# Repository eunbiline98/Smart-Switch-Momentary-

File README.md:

# Smart Switch Momentary

DIY Smart Switch momentary 2 Gang and 2 Channel Relay SPDT

List Item

- Esp8266 (Wemos D1 Mini) / Chip SoC Esp8266
- Relay 5VDC SPDT Songle (Max Current 10A)
- Power Module Hi-Link 220VAC to 5VDC
- Resistor 1k, 10K (SMD 0805)
- Diode 1N4007 SMD
- Transistor 2n2222a
- Terminal Screw 6 Pin Hole
- Push Button (schneider momentary switch) Datasheet: https://download.schneider-electric.com/files?p_enDocType=Instruction+sheet&p_File_Name=MS18524.pdf&p_Doc_Ref=MS18524

# Schematic

# Layout 
### Top View 

### Bottom View

# Home Assistant

Under covers in HA, use this config

```
mqtt:
  broker: "Your IP Broker/server"
  port: Your port MQTT
  username: "Your username"
  password: Your password

switch:
  - platform: mqtt
    name: "General Lamp"
    state_topic: "switch/bedroom1/1/state"
    command_topic: "switch/1/command"
    payload_on: "1"
    payload_off: "0"

 switch:
  - platform: mqtt
    name: "Cove Lighting"
    state_topic: "switch/bedroom1/2/state"
    command_topic: "switch/2/command"
    payload_on: "1"
    payload_off: "0"
```

# Reference

- WiFi Manager (https://github.com/tzapu/WiFiManager)
- MQTT (https://github.com/knolleary/pubsubclient)

# Update

- DIY_switch_3_gang_Ver_1_0 (Test Board Circuit)
- DIY_switch_3_gang_Ver_1_0_WM (Update Feature WifI Manager)
- DIY_switch_3_gang_Ver_1_1_WM (Update Last State Condition Dashboard Home Assistant)
- DIY_switch_3_gang_Ver_1_2_WM (Update Feature WiFi and Mqtt Config Manager)

# Dimension

- L = 69,84 mm
- W = 70,87 mm

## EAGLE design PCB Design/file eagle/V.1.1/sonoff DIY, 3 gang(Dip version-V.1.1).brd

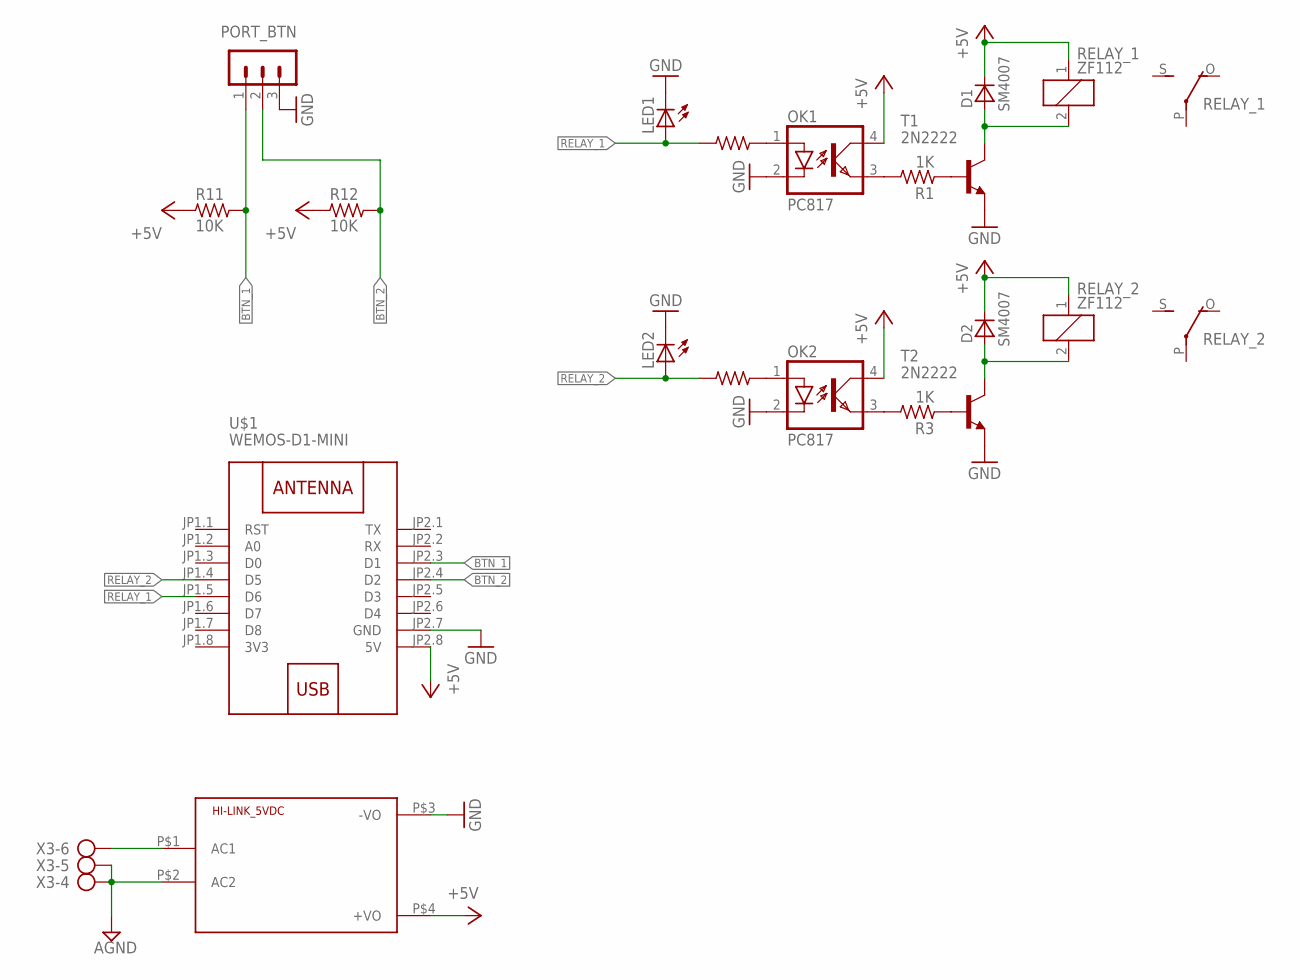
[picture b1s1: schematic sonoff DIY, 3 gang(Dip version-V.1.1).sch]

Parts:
D1, D2: SM4007; MELF-MLL41
HI-LINK_5VDC: HLK-PM013W; HLK-PM01
LED1, LED2: LED3MM
OK1, OK2: PC817; DIL04
PORT_BTN: MA03-1
R1, R2, R3, R4: 1K; R0805
R11, R12: 10K; R0805
RELAY_1, RELAY_2: ZF112
T1, T2: 2N2222; TO18
U$1: WEMOS-D1-MINI
X3: SMKDSP_1,5/6

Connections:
3V3: U$1.JP1.8 (3V3)
+5V: D1.C, D2.C, HI-LINK_5VDC.P$4 (+VO), OK1.4 (COL), OK2.4 (COL), R11.1, R12.1, RELAY_1.1, RELAY_2.1, U$1.JP2.8 (5V)
AGND: HI-LINK_5VDC.P$2 (AC2), X3.4, X3.5
BTN_1: PORT_BTN.1, R11.2, U$1.JP2.3 (D1)
BTN_2: PORT_BTN.2, R12.2, U$1.JP2.4 (D2)
GND: HI-LINK_5VDC.P$3 (-VO), LED1.K (C), LED2.K (C), OK1.2 (C), OK2.2 (C), PORT_BTN.3, T1.1 (E), T2.1 (E), U$1.JP2.7 (GND)
unnamed: OK1.1 (A), R2.1
unnamed: OK1.3 (EMIT), R1.2
unnamed: R1.1, T1.2 (B)
unnamed: D1.A, RELAY_1.2, T1.3 (C)
unnamed: OK2.1 (A), R4.1
unnamed: HI-LINK_5VDC.P$1 (AC1), X3.6
unnamed: OK2.3 (EMIT), R3.2
unnamed: R3.1, T2.2 (B)
unnamed: D2.A, RELAY_2.2, T2.3 (C)
RELAY_1: LED1.A, R2.2, U$1.JP1.5 (D6)
RELAY_2: LED2.A, R4.2, U$1.JP1.4 (D5)

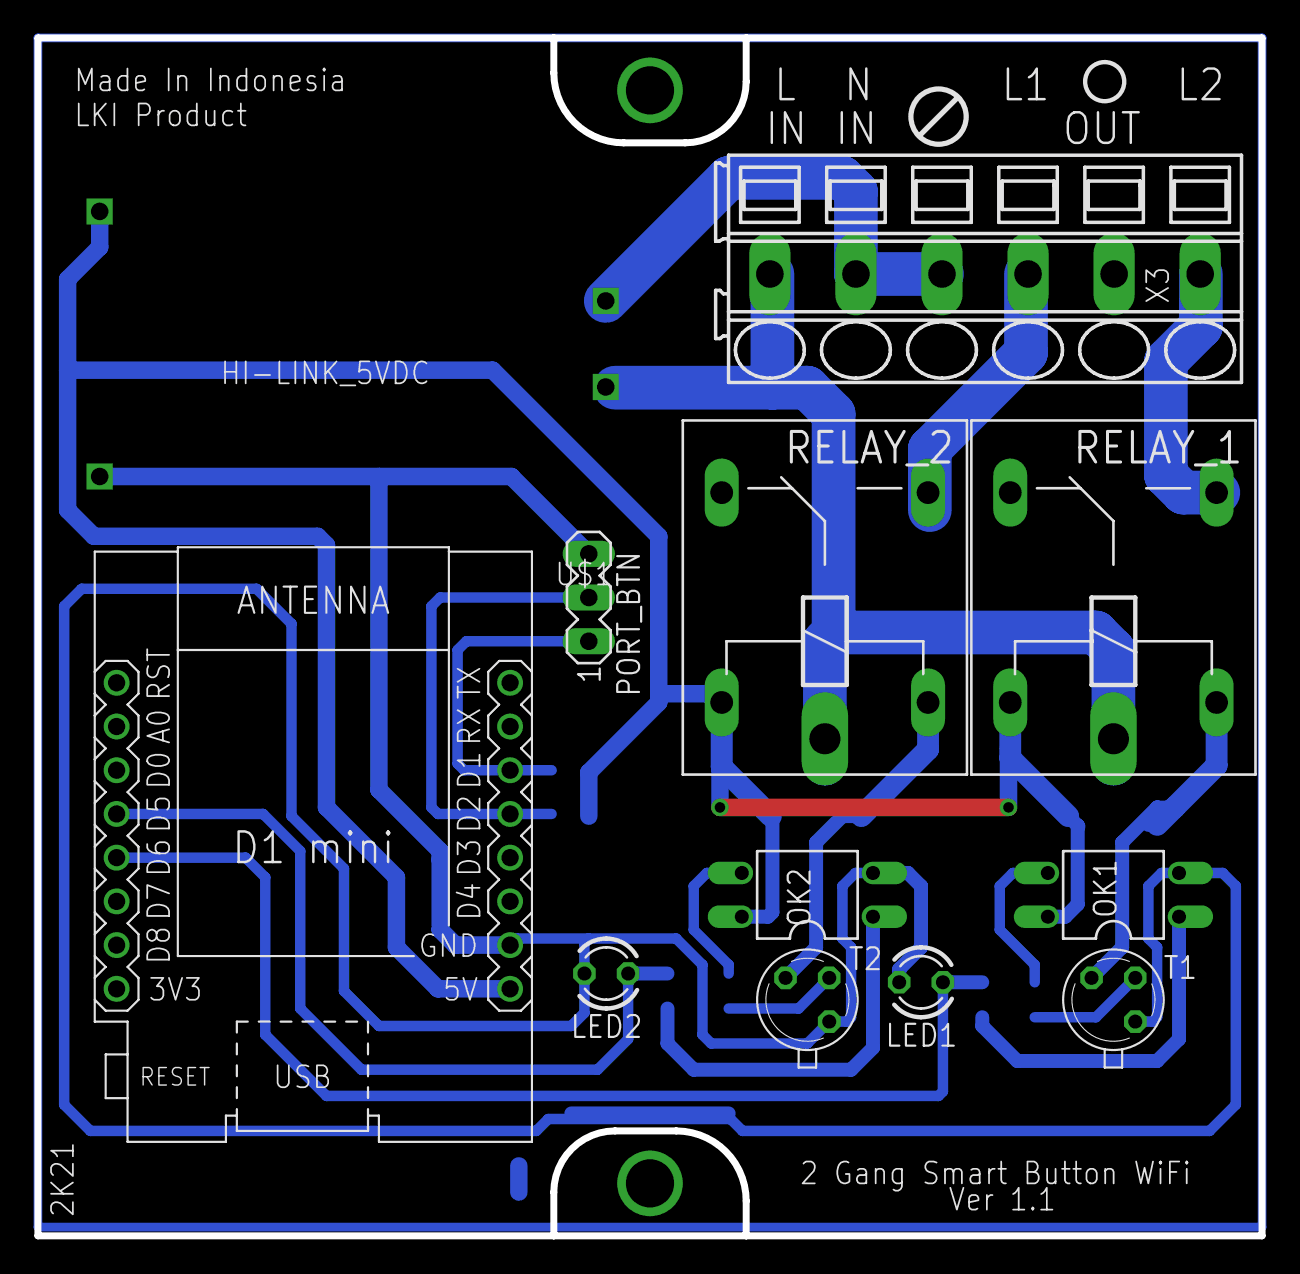
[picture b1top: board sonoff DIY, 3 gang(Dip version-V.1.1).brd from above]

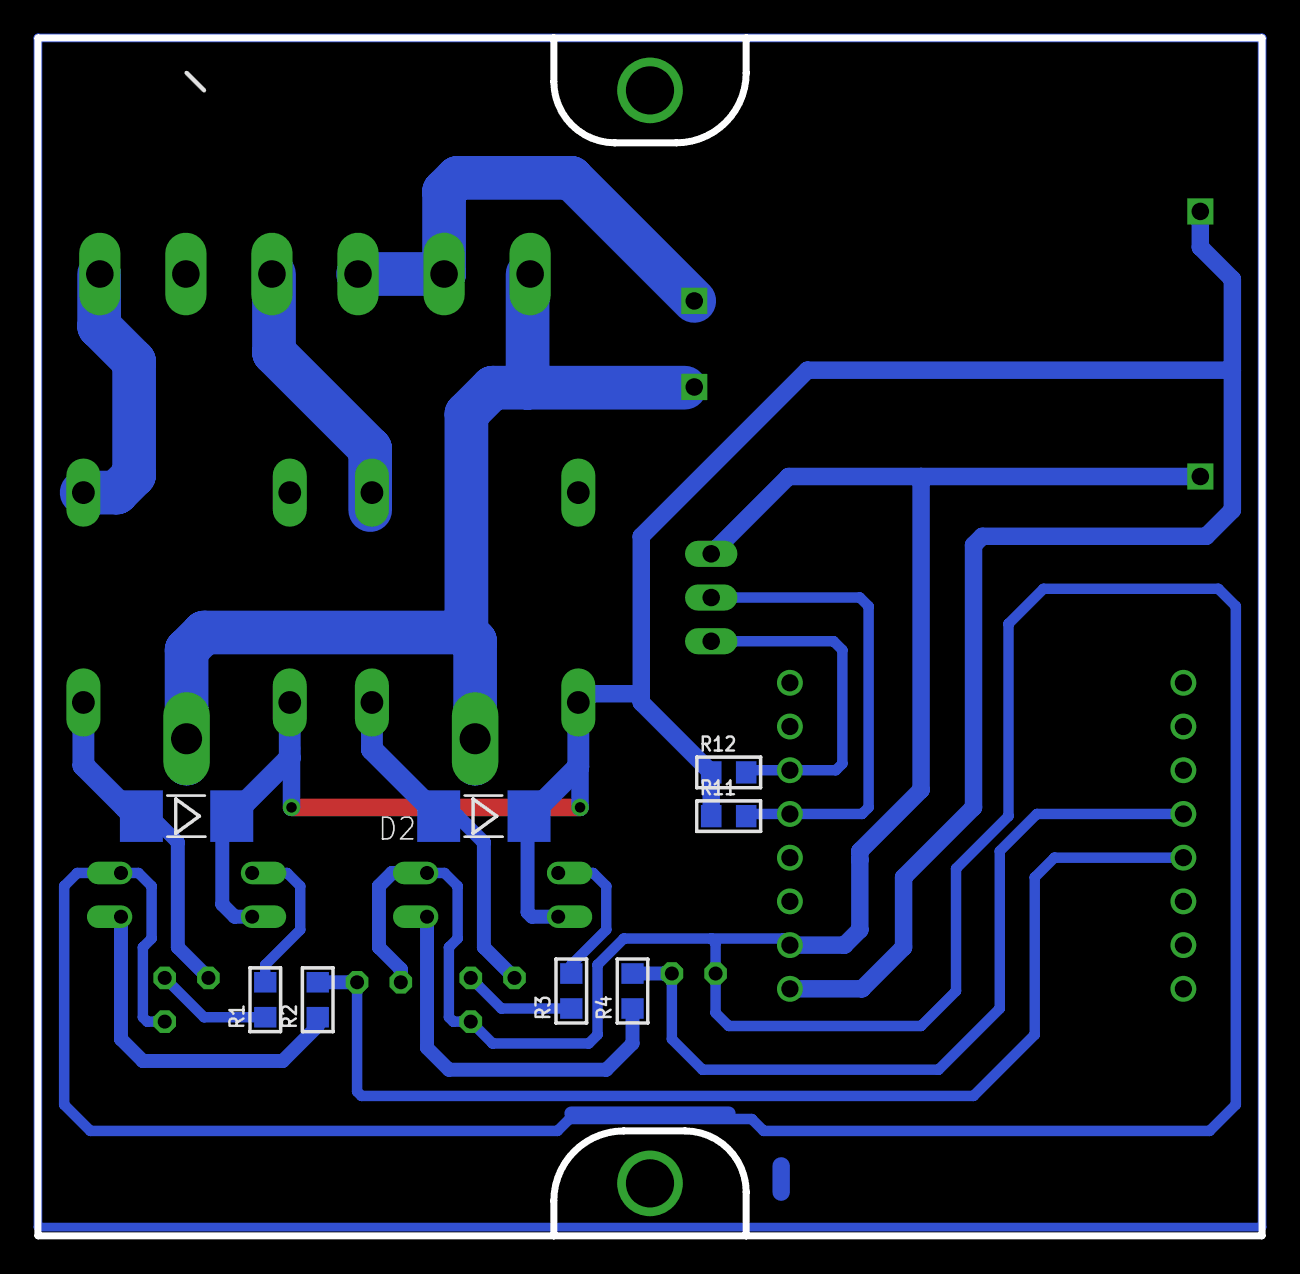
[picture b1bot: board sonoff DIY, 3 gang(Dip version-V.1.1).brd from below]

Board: 2 copper layers, 71.1 x 69.6 mm, 20 parts (8 on the bottom side), 16 nets.

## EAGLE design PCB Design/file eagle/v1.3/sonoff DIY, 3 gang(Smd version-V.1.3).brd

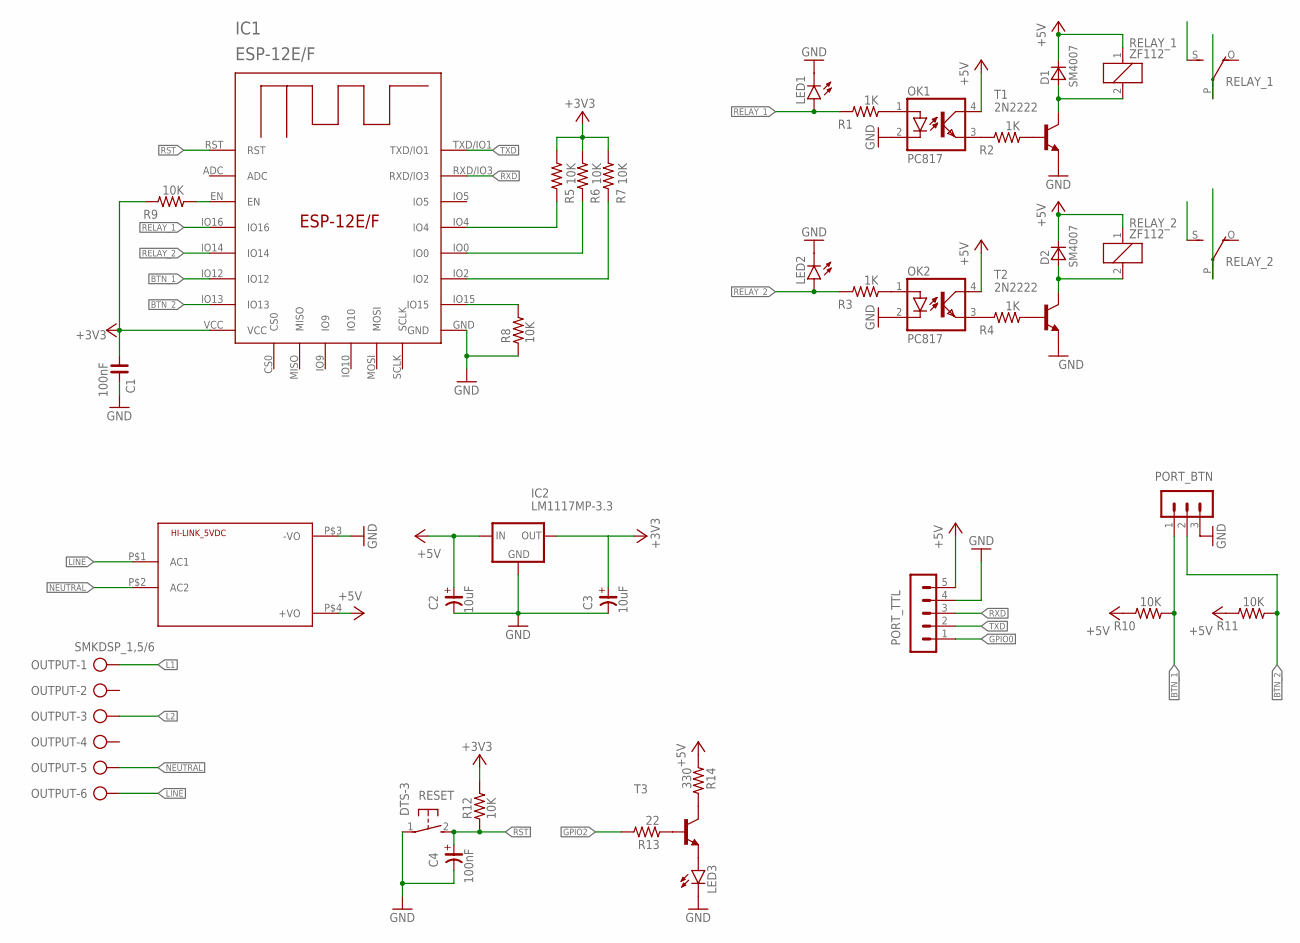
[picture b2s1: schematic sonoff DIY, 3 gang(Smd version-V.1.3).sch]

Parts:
C1: 100nF; C0805
C2, C3: 10uF; C3528/T
C4: 100nF; C3528/T
D1, D2: SM4007; MELF-MLL41
HI-LINK_5VDC: HLK-PM013W; HLK-PM01
IC1: ESP-12E/F; ESP-12E
IC2: LM1117MP-3.3; SOT223
LED1, LED2, LED3: LED3MM
OK1, OK2: PC817; DIL04
OUTPUT: SMKDSP_1,5/6
PORT_BTN: MA03-1
PORT_TTL: MA05-1
R1, R2, R3, R4: 1K; R0805
R5, R6, R7, R8, R9, R10, R11, R12: 10K; R0805
R13: 22; R0805
R14: 330; R0805
RELAY_1, RELAY_2: ZF112
RESET: DTS-3
T1, T2: 2N2222; TO18
T3: BC817-16LT1-NPN-SOT23-BEC; SOT23-BEC

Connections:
+3V3: C1.1, C3.+, IC1.VCC, IC2.2 (OUT), IC2.4 (OUT), R5.1, R6.1, R7.1, R9.2, R12.2
+5V: C2.+, D1.C, D2.C, HI-LINK_5VDC.P$4 (+VO), IC2.3 (IN), OK1.4 (COL), OK2.4 (COL), PORT_TTL.5, R10.2, R11.2, R14.1, RELAY_1.1, RELAY_2.1
BTN_1: IC1.IO12, PORT_BTN.1, R10.1
BTN_2: IC1.IO13, PORT_BTN.2, R11.1
GND: C1.2, C2.-, C3.-, C4.-, HI-LINK_5VDC.P$3 (-VO), IC1.GND, IC2.1 (GND), LED1.K (C), LED2.K (C), LED3.K (C), OK1.2 (C), OK2.2 (C), PORT_BTN.3, PORT_TTL.4, R8.1, RESET.1, T1.1 (E), T2.1 (E)
GPIO0: IC1.IO0, PORT_TTL.1, R6.2
GPIO2: IC1.IO2, R7.2, R13.2
L1: OUTPUT.1, RELAY_1.S
L2: OUTPUT.3, RELAY_2.S
LINE: HI-LINK_5VDC.P$1 (AC1), OUTPUT.6, RELAY_1.P, RELAY_2.P
unnamed: OK1.3 (EMIT), R2.2
unnamed: R2.1, T1.2 (B)
unnamed: OK2.1 (A), R3.1
unnamed: D1.A, RELAY_1.2, T1.3 (C)
unnamed: OK2.3 (EMIT), R4.2
unnamed: R4.1, T2.2 (B)
unnamed: OK1.1 (A), R1.1
unnamed: IC1.IO4, R5.2
unnamed: D2.A, RELAY_2.2, T2.3 (C)
unnamed: LED3.A, T3.E
unnamed: IC1.IO15, R8.2
unnamed: R13.1, T3.B
unnamed: IC1.EN, R9.1
unnamed: R14.2, T3.C
NEUTRAL: HI-LINK_5VDC.P$2 (AC2), OUTPUT.5
RELAY_1: IC1.IO16, LED1.A, R1.2
RELAY_2: IC1.IO14, LED2.A, R3.2
RST: C4.+, IC1.RST, R12.1, RESET.2
RXD: IC1.RXD/IO3, PORT_TTL.3
TXD: IC1.TXD/IO1, PORT_TTL.2

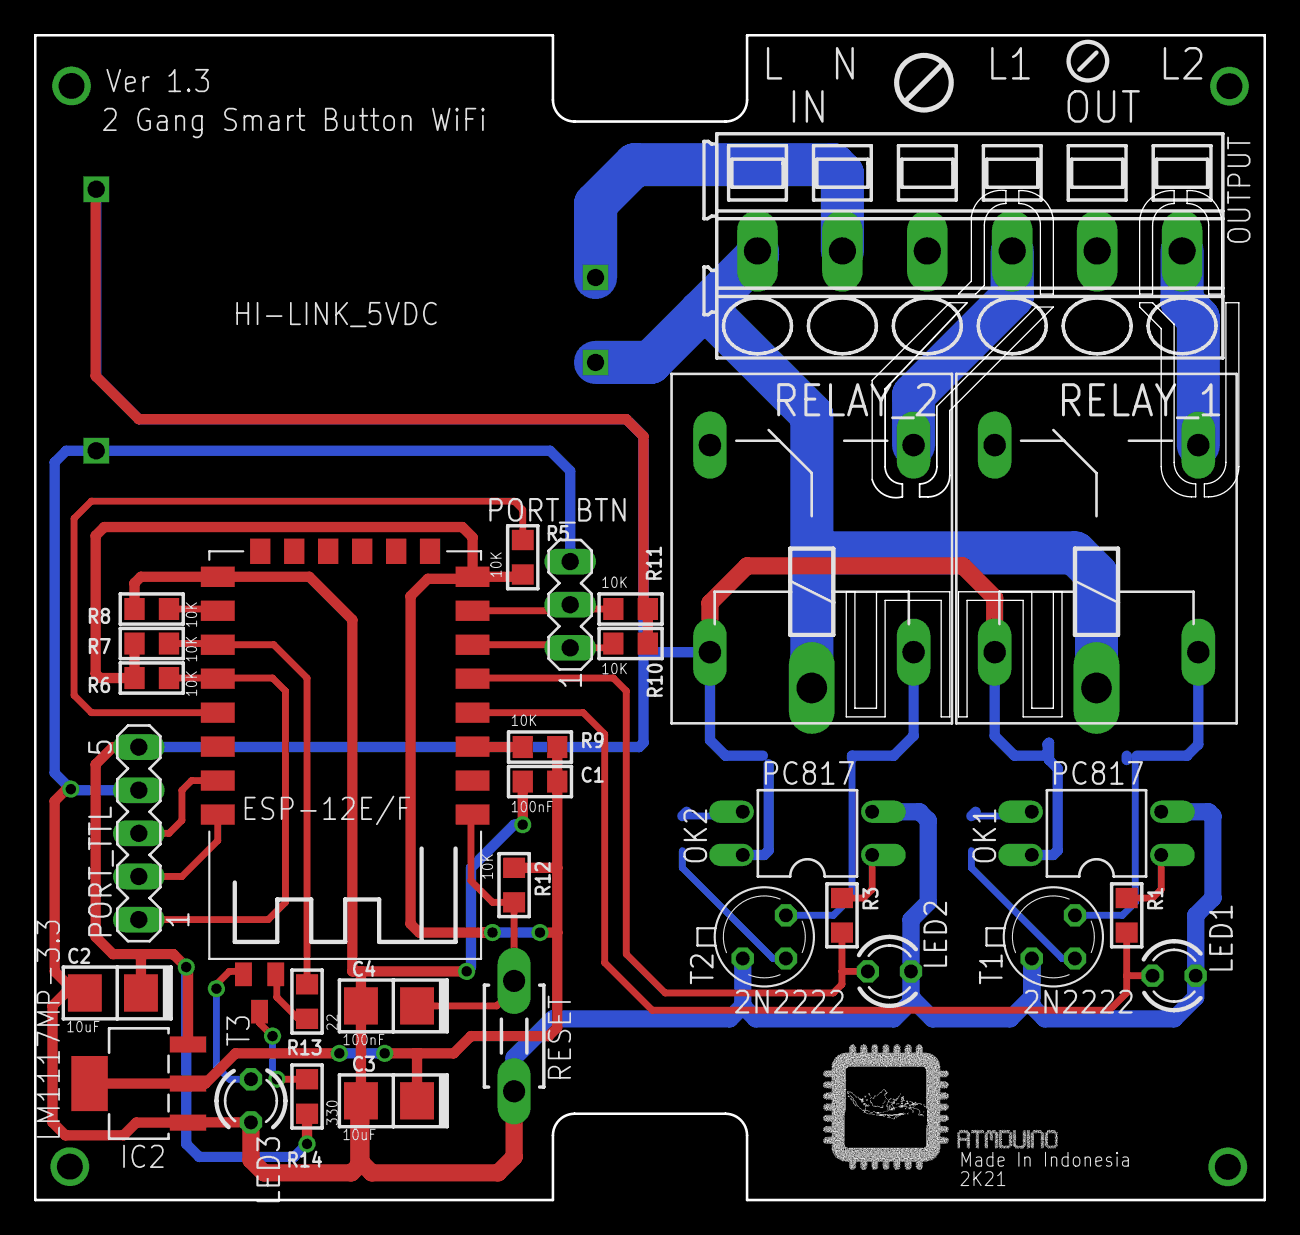
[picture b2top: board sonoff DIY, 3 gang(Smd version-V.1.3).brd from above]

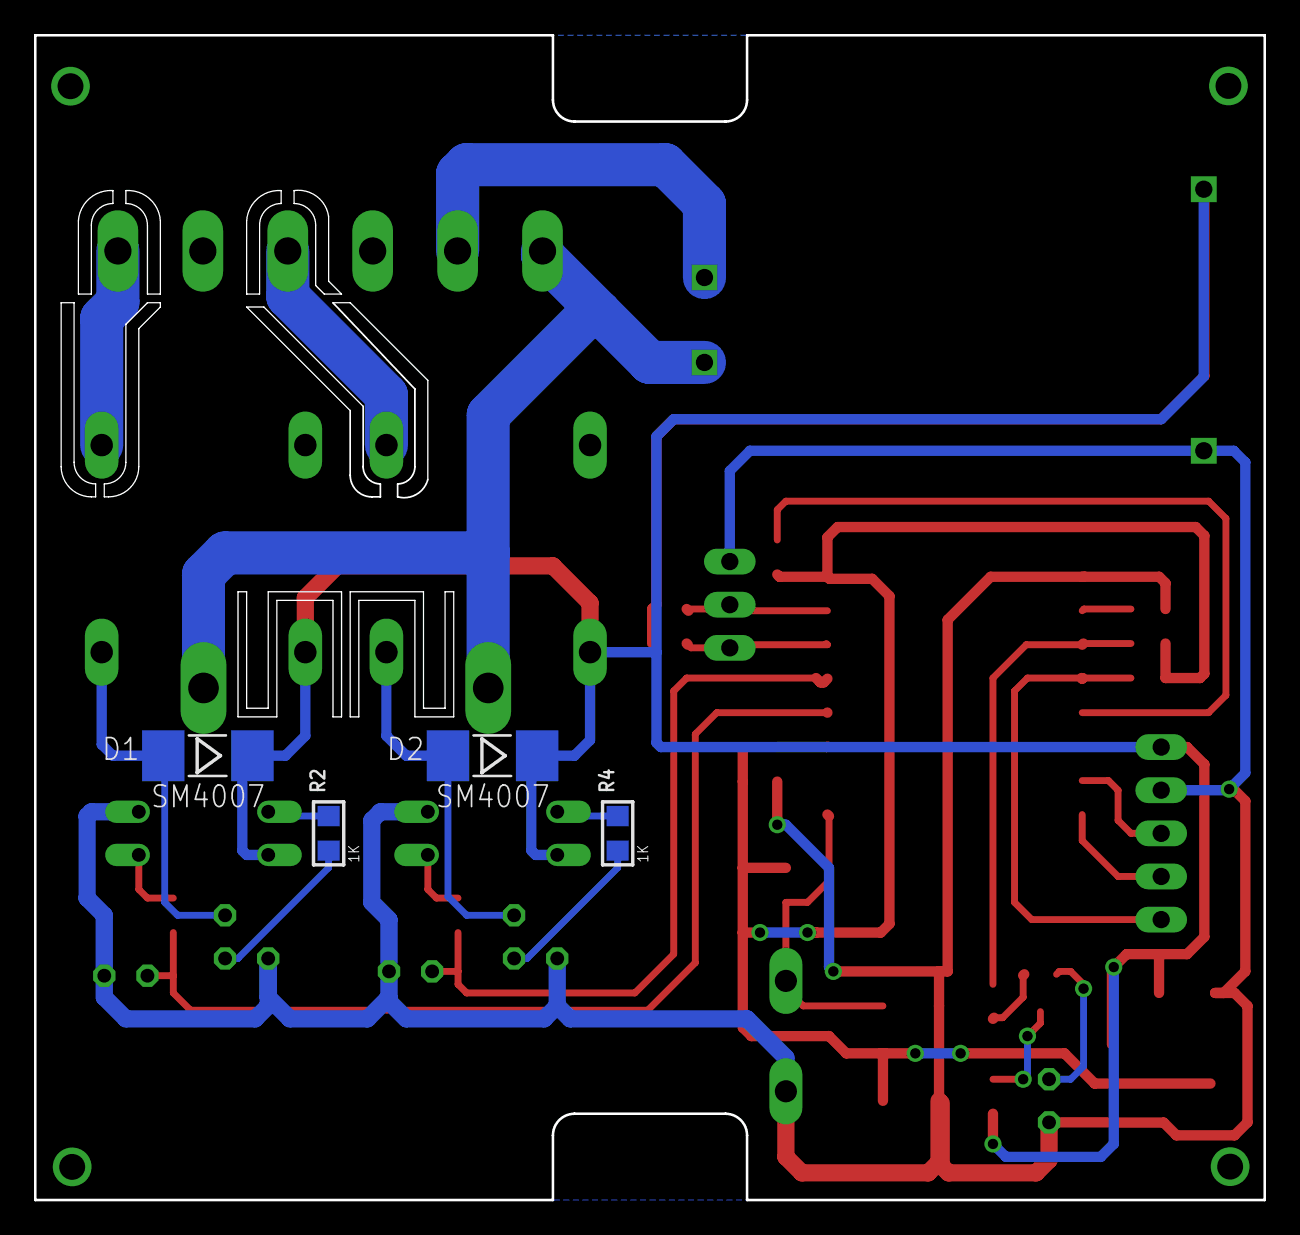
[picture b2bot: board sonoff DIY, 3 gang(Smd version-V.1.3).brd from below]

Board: 2 copper layers, 72.4 x 68.6 mm, 37 parts (4 on the bottom side), 30 nets.

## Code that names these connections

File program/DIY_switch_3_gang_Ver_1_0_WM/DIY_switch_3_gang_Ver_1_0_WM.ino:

#include <ESP8266WiFi.h>
#include <PubSubClient.h>
#include <WiFiManager.h>
#include <Ticker.h>

const char *MQTT_SERVER = "192.168.x.xxx";
const char *MQTT_TOPIC = "switch/bedroom/1";

const char *MQTT_CLIENT_ID = "switch_bedroom1";
const char *MQTT_USERNAME = ".........";
const char *MQTT_PASSWORD = "..........";

WiFiClient espClient;
PubSubClient client(espClient);
Ticker ticker;

// Pin Setup
#define relay_1 14
#define relay_2 12
#define btn_1 5
#define btn_2 4

int flag1 = 0;
int flag2 = 0;
int state1 = 0;
int state2 = 0;

int lastMilis = 0;
unsigned long nowMillis = millis();

void tick()
{
  //toggle state
  digitalWrite(2, !digitalRead(2)); // set pin GPIO2 Led Wemos On-board
}

void configModeCallback(WiFiManager *myWiFiManager)
{
  Serial.println("Entered config mode");
  Serial.println(WiFi.softAPIP());
  //if you used auto generated SSID, print it
  Serial.println(myWiFiManager->getConfigPortalSSID());
  //entered config mode, make led toggle faster
  ticker.attach(0.2, tick);
}

void setup_wifi()
{
  WiFi.mode(WIFI_STA);
  pinMode(2, OUTPUT);
  ticker.attach(0.6, tick);

  WiFiManager wm;
  wm.setAPCallback(configModeCallback);
  //
  //  bool res;
  //  res = wm.autoConnect("LKI Smart Button WiFi", "lki2021");

  if (!wm.autoConnect())
  { // SSID from IDChip
    Serial.println("failed to connect");
    //    wm.resetSettings();
    ESP.restart();
    delay(1000);
  }

  Serial.println("connected...");
  ticker.detach();
  digitalWrite(2, LOW);
}

void button_func()
{
  // button1
  int stateBtn_1 = digitalRead(btn_1);
  if (!stateBtn_1 && !flag1)
  {
    if (state1 == 0)
    {
      client.publish(MQTT_TOPIC, "1");
      state1 = 1;
    }
    else
    {
      client.publish(MQTT_TOPIC, "2");
      state1 = 0;
    }
    flag1 = 1;
  }
  else if (stateBtn_1 && flag1)
  {
    flag1 = 0;
  }
  // button2
  int stateBtn_2 = digitalRead(btn_2);
  if (!stateBtn_2 && !flag2)
  {
    if (state2 == 0)
    {
      client.publish(MQTT_TOPIC, "3");
      state2 = 1;
    }
    else
    {
      client.publish(MQTT_TOPIC, "4");
      state2 = 0;
    }
    flag2 = 1;
  }
  else if (stateBtn_2 && flag2)
  {
    flag2 = 0;
  }
  delay(100);
}

void callback(char *topic, byte *message, unsigned int length)
{
  Serial.print("Message arrived in topic: ");
  Serial.println(topic);
  Serial.print("Message:");
  String messageTemp;

  if (String(topic) != MQTT_TOPIC)
  {
    return;
  }

  for (int i = 0; i < length; i++)
  {
    Serial.print((char)message[i]);
    if ((char)message[i] != '"')
      messageTemp += (char)message[i];
  }
  // Changes the output state according to the message
  Serial.println("");
  Serial.print("Changing output to ");
  //  Serial.println(messageTemp);
  if (messageTemp == "1")
  {
    Serial.println("Relay_1On");
    digitalWrite(relay_1, HIGH);
  }
  if (messageTemp == "2")
  {
    Serial.println("Relay_1Off");
    digitalWrite(relay_1, LOW);
  }
  if (messageTemp == "3")
  {
    Serial.println("Relay_2On");
    digitalWrite(relay_2, HIGH);
  }
  if (messageTemp == "4")
  {
    Serial.println("Relay_2Off");
    digitalWrite(relay_2, LOW);
  }
}

void reconnect()
{
  // Loop until we're reconnected
  while (!client.connected())
  {
    Serial.print("Attempting MQTT connection...");
    // Attempt to connect
    if (client.connect(MQTT_CLIENT_ID, MQTT_USERNAME, MQTT_PASSWORD))
    {
      Serial.println("connected");
      //subscribe
      client.subscribe(MQTT_TOPIC);
    }
    else
    {
      Serial.print("failed, rc=");
      Serial.print(client.state());
      Serial.println(" try again in 5 seconds");
      // Wait 5 seconds before retrying
      delay(5000);
    }
  }
}

void setup()
{
  // Serial port for debugging purposes
  Serial.begin(115200);
  setup_wifi();

  // MQTT Server Setup
  client.setServer(MQTT_SERVER, 1883);
  client.setCallback(callback);

  pinMode(2, OUTPUT); //WiFi Indicator
  pinMode(relay_1, OUTPUT);
  pinMode(relay_2, OUTPUT);

  pinMode(btn_1, INPUT);
  pinMode(btn_2, INPUT);
}

void loop()
{
  if (!client.connected())
  {
    reconnect();
  }
  button_func();
  client.loop();
}

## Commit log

2021-10-10 Intial Commit
2021-10-17 Update Setup HomeAssistant
2021-10-17 update setup home assiatant
2021-11-05 Update Fix
2021-11-05 Update WiFi and Mqtt Manager
2021-11-05 Readme Update
2021-11-11 Udate fix mqtt port config
2021-12-07 Upload Websocket Test
2021-12-07 Upload Test Client Connection
2021-12-07 Adding Websocket Test
2021-12-07 Adding Client Connection Test
2021-12-11 Adding Websocket Mqtt
2022-01-22 Adding smd version
2022-02-18 Adding File Geber
2022-02-18 Adding Design PCB V1.3
2022-02-18 Adding Design PCB

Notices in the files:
parts and their libraries:
rc-master-smd: Copyright (C) 2007, Bob Starr
diy-modules: Released under the Creative Commons Attribution 4.0 International License: http://creativecommons.org/licenses/by/4.0
